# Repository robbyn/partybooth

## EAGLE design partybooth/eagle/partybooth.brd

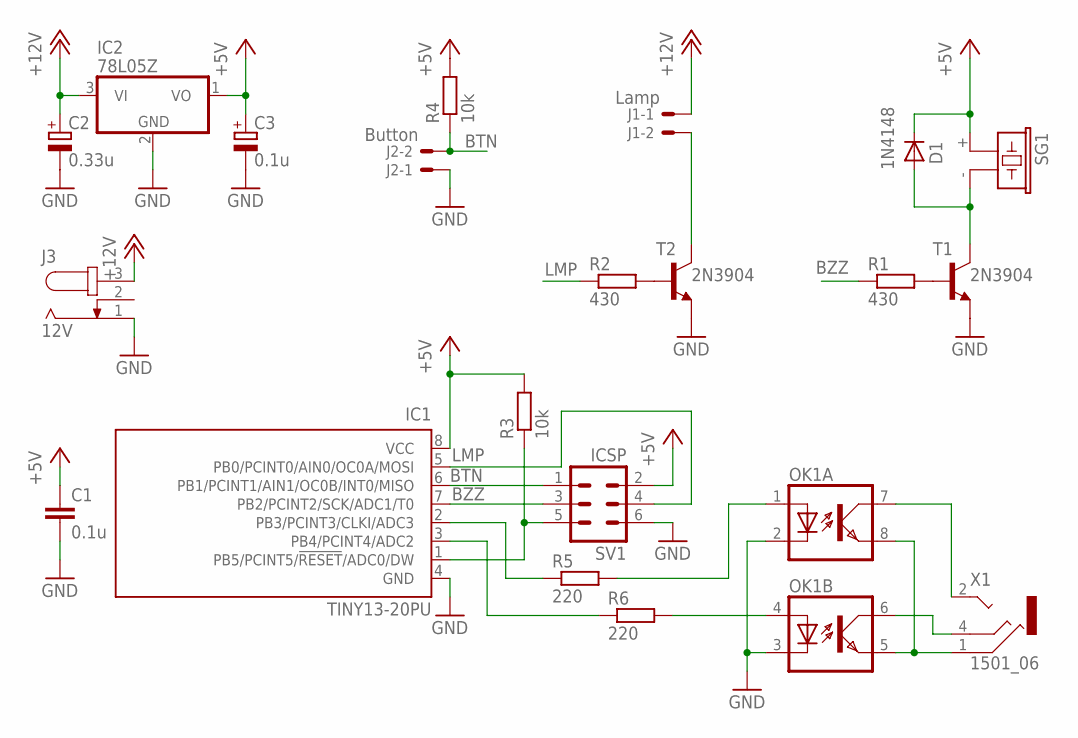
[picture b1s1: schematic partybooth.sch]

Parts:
C1: 0.1u; C050-025X075
C2: 0.33u; E5-6
C3: 0.1u; E5-5
D1: 1N4148; DO35-7
IC1: TINY13-20PU; DIL08
IC2: 78L05Z; TO92
J1: Lamp; 6410-02
J2: Button; 6410-02
J3: 12V; SPC4077
OK1: ILD2; DIL08
R1, R2: 430; 0204/7
R3, R4: 10k; 0204/7
R5, R6: 220; 0204/7
SG1: F/CM12P
SV1: ICSP; MA03-2
T1, T2: 2N3904; TO92
X1: 1501_06

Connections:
+5V: C1.1, C3.+, D1.C, IC1.8 (VCC), IC2.1 (VO), R3.2, R4.2, SG1.+ (1), SV1.2
+12V: C2.+, IC2.3 (VI), J1.1, J3.3
BTN: IC1.6 (PB1/PCINT1/AIN1/OC0B/INT0/MISO), J2.2, R4.1, SV1.1
BZZ: IC1.7 (PB2/PCINT2/SCK/ADC1/T0), R1.1, SV1.3
FOC: OK1.4 (A), R6.2
GND: C1.2, C2.-, C3.-, IC1.4 (GND), IC2.2 (GND), J2.1, J3.1, OK1.2 (C), OK1.3 (C), SV1.6, T1.3 (E), T2.3 (E)
LMP: IC1.5 (PB0/PCINT0/AIN0/OC0A/MOSI), R2.1, SV1.4
unnamed: R1.2, T1.2 (B)
unnamed: D1.A, SG1.- (2), T1.1 (C)
unnamed: R2.2, T2.2 (B)
unnamed: J1.2, T2.1 (C)
unnamed: OK1.1 (A), R5.2
unnamed: IC1.1 (PB5/PCINT5/!RESET!/ADC0/DW), R3.1, SV1.5
unnamed: IC1.3 (PB4/PCINT4/ADC2), R6.1
unnamed: OK1.5 (EMIT), OK1.8 (EMIT), X1.1
unnamed: OK1.6 (COL), X1.4 (3)
unnamed: OK1.7 (COL), X1.2
SHT: IC1.2 (PB3/PCINT3/CLKI/ADC3), R5.1

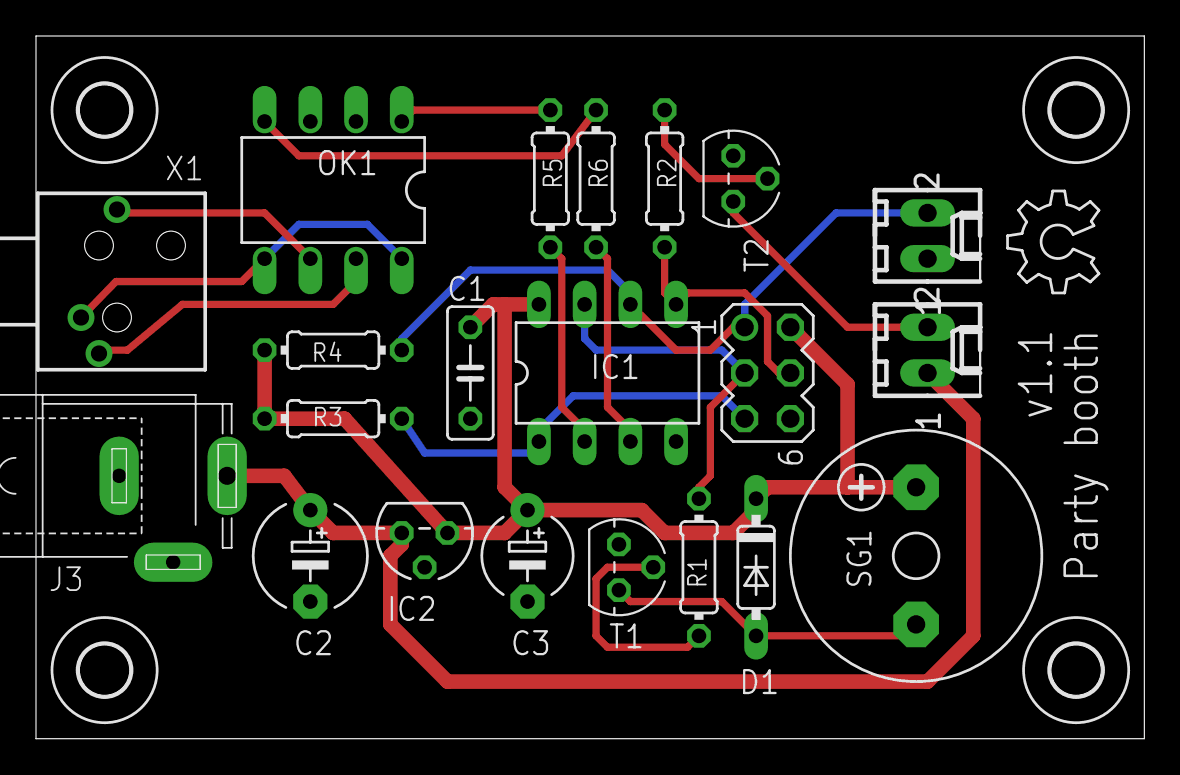
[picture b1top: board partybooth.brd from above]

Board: 2 copper layers, 61.6 x 39.0 mm, 26 parts (0 on the bottom side), 18 nets.

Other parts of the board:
U$1: OSHW_6X200_NOTEXT
U$2, U$3, U$4, U$5: 2,8

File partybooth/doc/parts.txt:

Partlist

Exported from partybooth.sch at 4/10/12 3:43 PM

EAGLE Version 6.1.0 Copyright (c) 1988-2012 CadSoft

Assembly variant: 

Part     Value          Device          Package      Library     Sheet

C1       0.1u           C-EU050-025X075 C050-025X075 rcl         1
C2       100u           CPOL-EUB45181B  B45181B      rcl         1
C3       10u            CPOL-EUB45181B  B45181B      rcl         1
D1       1N4148         1N4148DO35-7    DO35-7       diode       1
IC1      TINY13-20PU    TINY13-20PU     DIL08        atmel       1
IC2      78L05Z         78L05Z          TO92         linear      1
J1       Lamp           22-27-2021-02   6410-02      con-molex   1
J2       Button         22-27-2021-02   6410-02      con-molex   1
J3       12V            JACK-PLUG0      SPC4077      con-jack    1
OK1                     ILD2            DIL08        optocoupler 1
R1       430            R-EU_0204/7     0204/7       rcl         1
R2       430            R-EU_0204/7     0204/7       rcl         1
R3       10k            R-EU_0204/7     0204/7       rcl         1
R4       10k            R-EU_0204/7     0204/7       rcl         1
R5       220            R-EU_0204/7     0204/7       rcl         1
R6       220            R-EU_0204/7     0204/7       rcl         1
SG1                     F/CM12P         F/CM12P      buzzer      1
SV1      ICSP           MA03-2          MA03-2       con-lstb    1
T1       2N3904         2N3904          TO92         transistor  1
T2       2N3904         2N3904          TO92         transistor  1
X1       1501_06        1501_06         1501_06      con-lumberg 1

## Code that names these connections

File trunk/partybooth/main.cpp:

#include "common.h"
#include <avr/io.h>
#include <avr/sleep.h>
#include <avr/interrupt.h>

static const uint8_t LED = PB0;
static const uint8_t BTN = PB1;
static const uint8_t BZZ = PB2;
static const uint8_t SHT = PB3;

static uint8_t state = 0;
static uint16_t counter = 0;

ISR(TIM0_COMPA_vect) {
    OCR0A ^= 1;
    ++counter;
    switch (state) {
        case 2:
        case 4:
        case 6:
        case 8:
            if (counter >= 3200) {
                counter = 0;
                ++state;
                PORTB |= 1 << LED;
            }
            break;
        case 1:
        case 3:
        case 5:
        case 7:
            if (counter >= 800) {
                counter = 0;
                ++state;
                PORTB &= ~((1 << LED) | (1 << BZZ));
            } else {
                PORTB ^= 1 << BZZ;
            }
            break;
        case 9:
            if (counter >= 4000) {
                counter = 0;
                ++state;
                PORTB &= ~((1 << LED) | (1 << BZZ));
                PORTB |= 1 << SHT;
            } else {
                PORTB ^= 1 << BZZ;
            }
            break;
        case 10:
            if (counter >= 800) {
                counter = 0;
                state = 0;
                PORTB &= ~(1 << SHT);
            }
            break;
    }
}

ISR(INT0_vect) {
    counter = 0;
    state = 1;
    PORTB &= ~(1 << SHT);
    PORTB |= 1 << LED;
}

int main() {
    DDRB |= (1 << LED) | (1 << BZZ) | (1 << BZZ); // LED, BZZ, SHT output
    // Setup timer 0 for a frequency of 4kHz
    TCCR0A = 2; // top = OCRA
    TCCR0B = 2; // /8 prescale in addition to the /8 system clock prescale
    OCR0A = 37; // alternate between 36 and 37 (the correct count is 36.5)
    TCNT0 = 0;
    TIMSK0 = 4; // Enable interrupt for compare match A
    // Setup BTN interrupt
    MCUCR |= 3; // interrupt on the rising edge
    GIMSK |= 1 << INT0; // enable interrupt from INT0
    sei();
    while (true) {
        sleep_mode();
    }
}

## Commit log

2012-03-25 Initial directory structure.
2012-03-25 Schematic
2012-04-11 Check upload integrity digest, and use java.util.logging instead of System.out
2012-04-11 Blah
2015-03-15 Migrating wiki contents from Google Code
